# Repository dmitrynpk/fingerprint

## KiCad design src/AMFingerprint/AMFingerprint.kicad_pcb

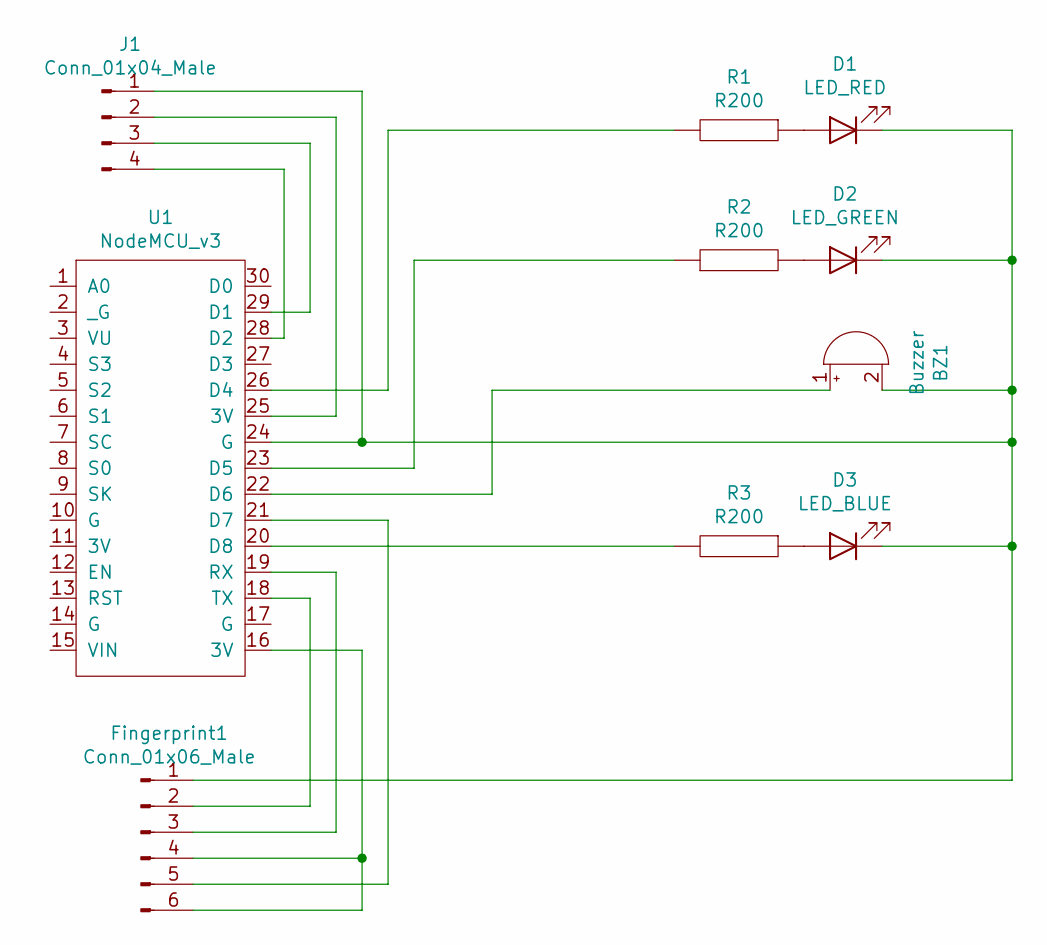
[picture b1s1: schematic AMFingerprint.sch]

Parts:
BZ1: Buzzer; Buzzer_12x9.5RM7.6
D1: LED_RED; LED_D5.0mm_Clear
D2: LED_GREEN; LED_D5.0mm_Clear
D3: LED_BLUE; LED_D5.0mm_Clear
Fingerprint1: Conn_01x06_Male; PinSocket_1x06_P2.00mm_Vertical
J1: Conn_01x04_Male; PinSocket_1x04_P2.00mm_Vertical
R1, R2, R3: R200; R_Axial_DIN0309_L9.0mm_D3.2mm_P12.70mm_Horizontal
U1: NodeMCU_v3; NodeMCU-LoLinV3

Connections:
unnamed: BZ1.1 (-), U1.22 (D6)
unnamed: BZ1.2 (+), D1.1 (K), D2.1 (K), D3.1 (K), Fingerprint1.1, J1.1, U1.24 (G)
unnamed: D1.2 (A), R1.1
unnamed: D2.2 (A), R2.2
unnamed: D3.2 (A), R3.1
unnamed: Fingerprint1.2, U1.18 (TX)
unnamed: Fingerprint1.3, U1.19 (RX)
unnamed: Fingerprint1.4, Fingerprint1.6, U1.16 (3V)
unnamed: Fingerprint1.5, U1.21 (D7)
unnamed: J1.2, U1.25 (3V)
unnamed: J1.3, U1.29 (D1)
unnamed: J1.4, U1.28 (D2)
unnamed: R1.2, U1.26 (D4)
unnamed: R2.1, U1.23 (D5)
unnamed: R3.2, U1.20 (D8)

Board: 2 copper layers, 10 parts (0 on the bottom side), 15 nets, no tracks yet.
